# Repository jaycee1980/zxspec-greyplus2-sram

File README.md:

# zxspec-greyplus2-sram
A replacement RAM module for a ZX Spectrum +2 (Grey) machine to replace 8x4164 chips

# What's it for ?
The grey +2 uses 4164 (64Kx1) DRAM as its system memory... there are two banks of it, one as "Contended" RAM, one as "Uncontended" RAM. This is similar in principle to the 4116 (16x1) DRAM and 4532 (32Kx1) DRAM in the original 48K spectrum. These chips can and do fail, and procuring replacements is getting more and more difficult.

For 48K spectrums, there are Lower and Upper RAM Replacement boards utilising modern 5V SRAM as a replacement. I couldn't find an equivalent solution for a grey +2 though.

So here we are! :)

# Building it
The gerber.zip file in this repository contains Gerber files needed by a PCB manufacturer to make the board. I personally use [JLCPCB](https://jlcpcb.com) but any PCB manufacturer should be able to produce it.

The [BOM file](/bom.txt) contains the parts needed to make the board. Please note that I have only personally used the Cypress CY62128ELL-45ZAXI memory at the moment, but the other SRAM listed there should also work. You *might* need to install C4 in some cases. My personal grey +2 worked just fine without it.

Also be aware that on the back of the PCB there is a jumper pad. This should be bridged such that the A pad is connected to the middle pad. You can use a solder blob, a short length of wire, or a 0 ohm resistor for this.

# License

If you wish to sell this please contact me at github@dark-matter.me.uk - I will usually grant permission provided they are sold for reasonable cost, and my name is not removed from the design.

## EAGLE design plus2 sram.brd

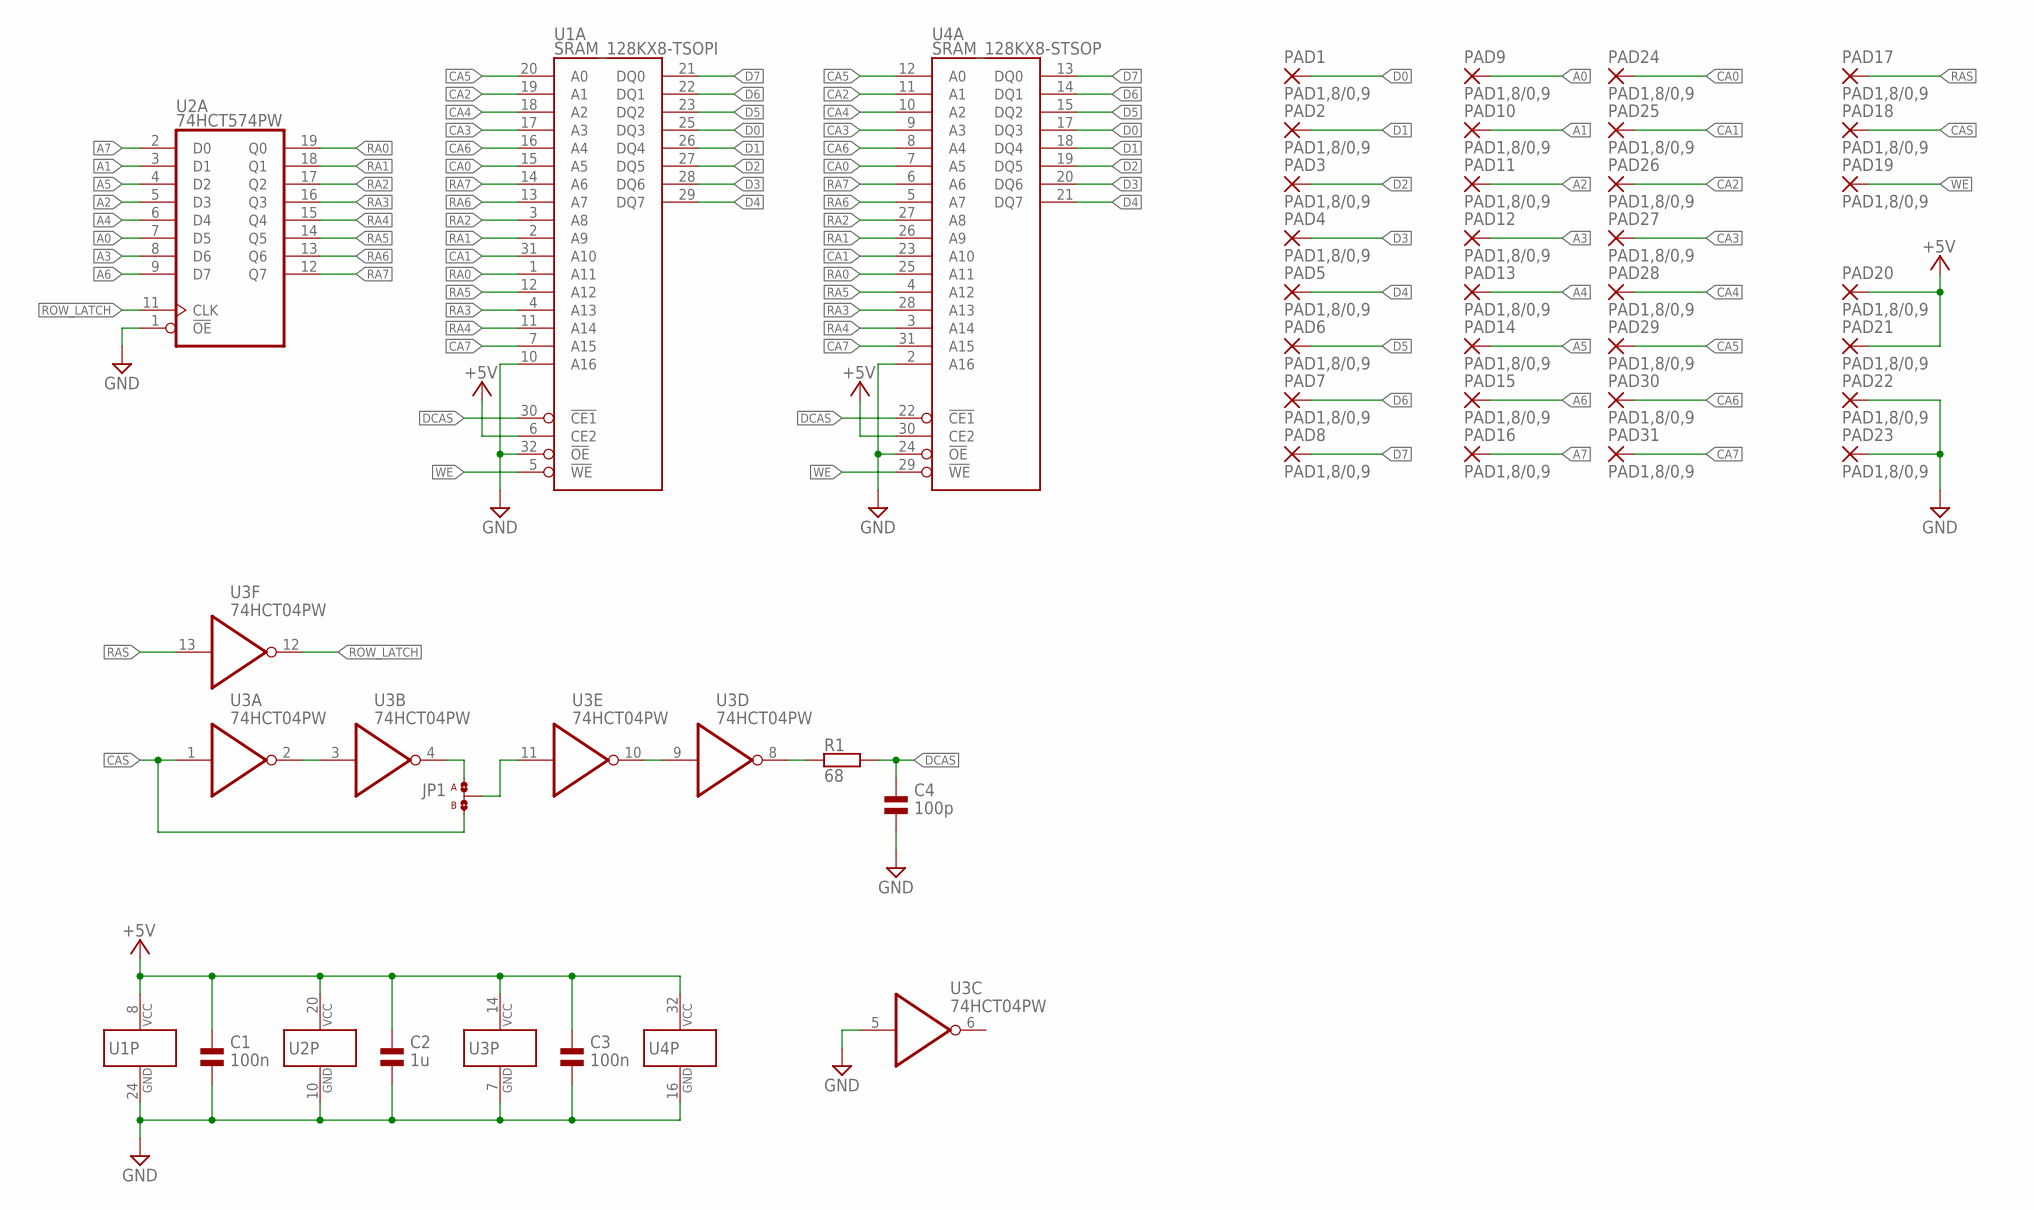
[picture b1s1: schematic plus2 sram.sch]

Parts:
C1, C3: 100n; 0603
C2: 1u; 0603
C4: 100p; 0603
JP1: JMP-SMD-3W0805; SJ-3P-0805
PAD1, PAD2, PAD3, PAD4, PAD5, PAD6, PAD7, PAD8, PAD9, PAD10, PAD11, PAD12, PAD13, PAD14, PAD15, PAD16, PAD17, PAD18, PAD19, PAD20, PAD21, PAD22, PAD23, PAD24, PAD25, PAD26, PAD27, PAD28, PAD29, PAD30, PAD31: PAD1,8/0,9; 1,8/0,9
R1: 68; 0603
U1: SRAM_128KX8-TSOPI; TSOP-I-32
U2: 74HCT574PW; TSSOP20
U3: 74HCT04PW; TSSOP14
U4: SRAM_128KX8-STSOP; STSOP-32

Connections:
!CAS: JP1.B, PAD18.1, U3.1 (I)
!DCAS: C4.1, R1.2, U1.30 (!CE1), U4.22 (!CE1)
!RAS: PAD17.1, U3.13 (I)
!WE: PAD19.1, U1.5 (!WE), U4.29 (!WE)
+5V: C1.1, C2.1, C3.1, PAD20.1, PAD21.1, U1.6 (CE2), U1.8 (VCC), U2.20 (VCC), U3.14 (VCC), U4.30 (CE2), U4.32 (VCC)
A0: PAD9.1, U2.7 (D5)
A1: PAD10.1, U2.3 (D1)
A2: PAD11.1, U2.5 (D3)
A3: PAD12.1, U2.8 (D6)
A4: PAD13.1, U2.6 (D4)
A5: PAD14.1, U2.4 (D2)
A6: PAD15.1, U2.9 (D7)
A7: PAD16.1, U2.2 (D0)
CA0: PAD24.1, U1.15 (A5), U4.7 (A5)
CA1: PAD25.1, U1.31 (A10), U4.23 (A10)
CA2: PAD26.1, U1.19 (A1), U4.11 (A1)
CA3: PAD27.1, U1.17 (A3), U4.9 (A3)
CA4: PAD28.1, U1.18 (A2), U4.10 (A2)
CA5: PAD29.1, U1.20 (A0), U4.12 (A0)
CA6: PAD30.1, U1.16 (A4), U4.8 (A4)
CA7: PAD31.1, U1.7 (A15), U4.31 (A15)
D0: PAD1.1, U1.25 (DQ3), U4.17 (DQ3)
D1: PAD2.1, U1.26 (DQ4), U4.18 (DQ4)
D2: PAD3.1, U1.27 (DQ5), U4.19 (DQ5)
D3: PAD4.1, U1.28 (DQ6), U4.20 (DQ6)
D4: PAD5.1, U1.29 (DQ7), U4.21 (DQ7)
D5: PAD6.1, U1.23 (DQ2), U4.15 (DQ2)
D6: PAD7.1, U1.22 (DQ1), U4.14 (DQ1)
D7: PAD8.1, U1.21 (DQ0), U4.13 (DQ0)
GND: C1.2, C2.2, C3.2, C4.2, PAD22.1, PAD23.1, U1.10 (A16), U1.24 (GND), U1.32 (!OE), U2.1 (!OE), U2.10 (GND), U3.5 (I), U3.7 (GND), U4.2 (A16), U4.16 (GND), U4.24 (!OE)
unnamed: R1.1, U3.8 (O)
unnamed: U3.2 (O), U3.3 (I)
unnamed: JP1.COM, U3.11 (I)
unnamed: U3.9 (I), U3.10 (O)
unnamed: JP1.A, U3.4 (O)
RA0: U1.1 (A11), U2.19 (Q0), U4.25 (A11)
RA1: U1.2 (A9), U2.18 (Q1), U4.26 (A9)
RA2: U1.3 (A8), U2.17 (Q2), U4.27 (A8)
RA3: U1.4 (A13), U2.16 (Q3), U4.28 (A13)
RA4: U1.11 (A14), U2.15 (Q4), U4.3 (A14)
RA5: U1.12 (A12), U2.14 (Q5), U4.4 (A12)
RA6: U1.13 (A7), U2.13 (Q6), U4.5 (A7)
RA7: U1.14 (A6), U2.12 (Q7), U4.6 (A6)
ROW_LATCH: U2.11 (CLK), U3.12 (O)

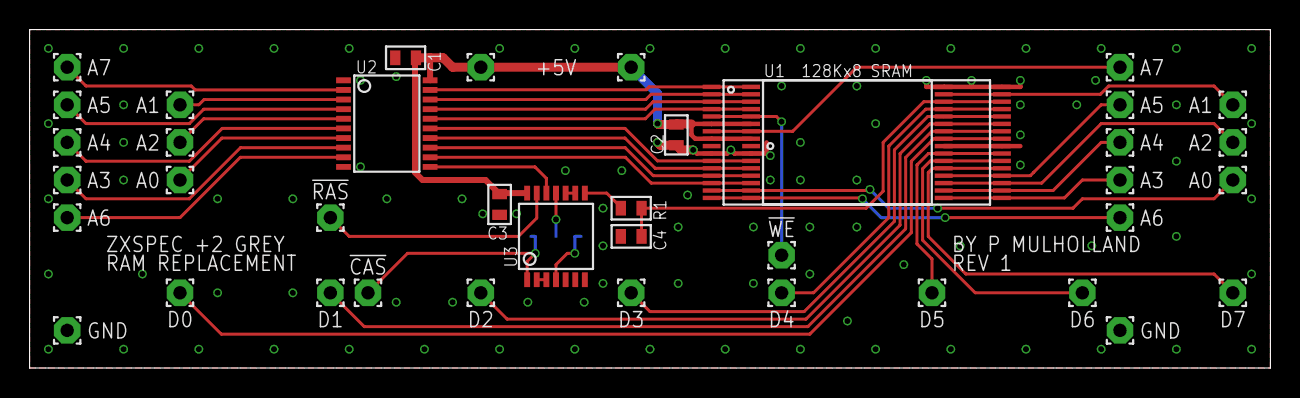
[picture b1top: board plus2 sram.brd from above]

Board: 2 copper layers, 83.8 x 22.9 mm, 41 parts (1 on the bottom side), 44 nets.

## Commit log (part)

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2026-03-14 Update LICENSE
2026-03-14 Content
